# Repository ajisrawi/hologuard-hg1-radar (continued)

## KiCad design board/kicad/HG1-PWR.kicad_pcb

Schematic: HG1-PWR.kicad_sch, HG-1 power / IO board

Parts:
C1: 100u 50V hold-up; CP_Elec_8x10
C2: 100u 50V; CP_Elec_8x10
C100: 47n; C_0402_1005Metric
C101, C104: 100n; C_0402_1005Metric
C102, C105: 1u; C_0402_1005Metric
C103: 47u; C_0805_2012Metric
C106, C108: 4.7u; C_0402_1005Metric
C107: 10u 50V; C_1210_3225Metric
CCH100: 10n 2kV; C_0805_2012Metric
D1: SMCJ36CA; D_SMC
H1, H2, H3, H4: M3; MountingHole_3.2mm_M3_Pad_Via
J1: M12 A-coded 8p power/IO; M12_8P_PCB
J2: M12 X-coded Ethernet; M12_8P_PCB
J3: Micro-Fit to ANT; Molex_Micro-Fit_3.0_43650-0400_1x04_P3.00mm_Horizontal
J4: Micro-Fit to DSP; Molex_Micro-Fit_3.0_43650-0400_1x04_P3.00mm_Horizontal
J5: FFC to DSP; Hirose_FH12-30S-0.5SH_1x30-1MP_P0.50mm_Horizontal
J6: Radome / board heater 10 W; JST_PH_B2B-PH-K_1x02_P2.00mm_Vertical
L1: DM filter 4.7u; L_12x12mm_H6mm
L2: XAL6030 4.7u; L_Coilcraft_XAL6030-XXX
L3: 10u 6A; L_12x12mm_H6mm
L4: 10u; L_0805_2012Metric
L5: XAL6030 2.2u; L_Coilcraft_XAL6030-XXX
Q1: N-MOSFET 80 V pass FET; SOIC-8_3.9x4.9mm_P1.27mm
Q2, Q3, Q4, Q5: N-MOSFET 60 V; SOIC-8_3.9x4.9mm_P1.27mm
Q6: N-MOSFET heater switch; SOIC-8_3.9x4.9mm_P1.27mm
R100, R102, R104, R116: 100k; R_0402_1005Metric
R101: 10k; R_0402_1005Metric
R103: 2.7k; R_0402_1005Metric
R105: 3.3k; R_0402_1005Metric
R106, R109, R113: 1M; R_0402_1005Metric
R107: 73.2k; R_0402_1005Metric
R108, R111: 18.2k; R_0402_1005Metric
R110: 191k; R_0402_1005Metric
R112: 4m 1%; R_0402_1005Metric
R114: 35.7k; R_0402_1005Metric
R115: 402k; R_0402_1005Metric
RCH100: 1M; R_0402_1005Metric
RHT100: 100k; R_0402_1005Metric
RS1: 5m 1%; R_0402_1005Metric
RV1: 150k; R_0402_1005Metric
RV2, RV4, RV5, RV6: 10k; R_0402_1005Metric
RV3: 100k; R_0402_1005Metric
T1: HX1188NL; GBE_MAG_16P
U1: LT4363; DFN-10-1EP_3x3mm_P0.5mm_EP1.65x2.38mm
U2: LT8640S 12 V; QFN-24-1EP_4x4mm_P0.5mm_EP2.6x2.6mm
U3: LT8390 28 V buck-boost; QFN-28-1EP_4x5mm_P0.5mm_EP2.65x3.65mm
U4: LT3462 -5 V; TSOT-23-6
U5: LT8640S 5 V; QFN-24-1EP_4x4mm_P0.5mm_EP2.6x2.6mm
U6: THVD1450; SOIC-8_3.9x4.9mm_P1.27mm

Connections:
+3V3_IO: J5.27, U6.8 (VCC)
+5V_RF: C2.1, J3.2, L4.1, L5.2, R109.1, RV5.1, U4.5 (VIN)
+12V_DSP: C103.1, J4.1, J4.2, L2.2, R106.1
+28V_PA: C107.1, J3.1, R112.2, R113.1, RV3.1, U3.6 (ISN)
-5V_BIAS: C108.1, J5.25, J5.26, R115.1, U4.6 (VOUT)
BG1: Q3.4 (G), U3.21 (BG1)
BG2: Q5.4 (G), U3.23 (BG2)
BST_5: C104.1, U5.13 (BST)
BST_12: C101.1, U2.13 (BST)
CHASSIS: CCH100.1, J1.S1 (SHELL), J1.S2 (SHELL), J1.S3 (SHELL), J1.S4 (SHELL), J2.S1 (SHELL), J2.S2 (SHELL), J2.S3 (SHELL), J2.S4 (SHELL), RCH100.1
DISC_IN: J1.8, J5.17
EN_28V: J5.18, U3.3 (EN/UVLO)
EN_HEATER: J5.21, Q6.4 (G), RHT100.1
EN_NEG5: J5.19, U4.4 (SHDN)
EN_RF_5V: J5.20, U5.3 (EN/UV)
FB_5: R109.2, R110.1, U5.4 (FB)
FB_12: R106.2, R107.1, U2.4 (FB)
FB_28: R113.2, R114.1, U3.4 (FB)
FB_NEG: R115.2, R116.1, U4.3 (FB)
FB_SURGE: R104.2, R105.1, U1.8 (FB)
GND: C1.2, C2.2, C100.2, C102.2, C103.2, C105.2, C106.2, C107.2, C108.2, CCH100.2, D1.2 (A2), H1.1, H2.1, H3.1, H4.1, J1.3, J1.4, J3.3, J3.4, J4.3, J4.4, J5.3, J5.6, J5.9, J5.12, J5.28, J5.29, J5.30, Q3.1 (S), Q3.2 (S), Q3.3 (S), Q5.1 (S), Q5.2 (S), Q5.3 (S), Q6.1 (S), Q6.2 (S), Q6.3 (S), R101.2, R103.2, R105.2, R107.2, R108.2, R110.2, R111.2, R114.2, R116.2, RCH100.2, RHT100.2, RV2.2, RV4.2, RV6.2, U1.5 (GND), U1.11 (GND), U2.17 (GND), U2.25 (GND), U3.13 (GND), U3.29 (GND), U4.2 (GND), U5.17 (GND), U5.25 (GND), U6.2 (~RE), U6.5 (GND)
HEATER_N: J6.2, Q6.5 (D), Q6.6 (D), Q6.7 (D), Q6.8 (D)
INTVCC_5: C105.1, U5.14 (INTVCC)
INTVCC_12: C102.1, U2.14 (INTVCC)
INTVCC_28: C106.1, U3.27 (INTVCC)
ISP_28: Q4.5 (D), Q4.6 (D), Q4.7 (D), Q4.8 (D), R112.1, U3.5 (ISP)
MDI_1: J2.1, T1.9 (CA+)
MDI_2: J2.2, T1.10 (CA-)
MDI_3: J2.3, T1.11 (CB+)
MDI_4: J2.4, T1.12 (CB-)
MDI_5: J2.5, T1.13 (CC+)
MDI_6: J2.6, T1.14 (CC-)
MDI_7: J2.7, T1.15 (CD+)
MDI_8: J2.8, T1.16 (CD-)
OV_DIV: R102.2, R103.1, U1.4 (OV)
PHY_MD1: J5.1, T1.1 (PA+)
PHY_MD2: J5.2, T1.2 (PA-)
PHY_MD3: J5.4, T1.3 (PB+)
PHY_MD4: J5.5, T1.4 (PB-)
PHY_MD5: J5.7, T1.5 (PC+)
PHY_MD6: J5.8, T1.6 (PC-)
PHY_MD7: J5.10, T1.7 (PD+)
PHY_MD8: J5.11, T1.8 (PD-)
PPS_EXT: J1.7, J5.16
RS485_A: J1.5, U6.6 (A)
RS485_B: J1.6, U6.7 (B)
RS485_DE: J5.15, U6.3 (DE)
RS485_RX: J5.14, U6.1 (R)
RS485_TX: J5.13, U6.4 (D)
RT_5: R111.1, U5.5 (RT)
RT_12: R108.1, U2.5 (RT)
SURGE_GATE: Q1.4 (G), U1.6 (GATE)
SW1_28: L3.1, Q2.1 (S), Q2.2 (S), Q2.3 (S), Q3.5 (D), Q3.6 (D), Q3.7 (D), Q3.8 (D), U3.24 (SW1)
SW2_28: L3.2, Q4.1 (S), Q4.2 (S), Q4.3 (S), Q5.5 (D), Q5.6 (D), Q5.7 (D), Q5.8 (D), U3.25 (SW2)
SW_5: C104.2, L5.1, U5.10 (SW), U5.11 (SW)
SW_12: C101.2, L2.1, U2.10 (SW), U2.11 (SW)
SW_NEG: L4.2, U4.1 (SW)
TG1: Q2.4 (G), U3.20 (TG1)
TG2: Q4.4 (G), U3.22 (TG2)
TMR: C100.1, U1.9 (TMR)
UV_DIV: R100.2, R101.1, U1.3 (UV)
V5_SENSE: J5.24, RV5.2, RV6.1
V28_SENSE: J5.23, RV3.2, RV4.1
VIN_FILT: C1.1, J6.1, L1.2, Q2.5 (D), Q2.6 (D), Q2.7 (D), Q2.8 (D), U2.1 (VIN), U2.2 (VIN), U2.3 (EN/UV), U3.1 (VIN), U3.2 (VIN), U5.1 (VIN), U5.2 (VIN)
VIN_PROT: L1.1, R104.1, RS1.2, RV1.1, U1.7 (OUT)
VIN_RAW: D1.1 (A1), J1.1, J1.2, Q1.5 (D), Q1.6 (D), Q1.7 (D), Q1.8 (D), R100.1, R102.1, U1.1 (VCC)
VIN_SENSE: J5.22, RV1.2, RV2.1
VIN_SNS: Q1.1 (S), Q1.2 (S), Q1.3 (S), RS1.1, U1.2 (SNS)

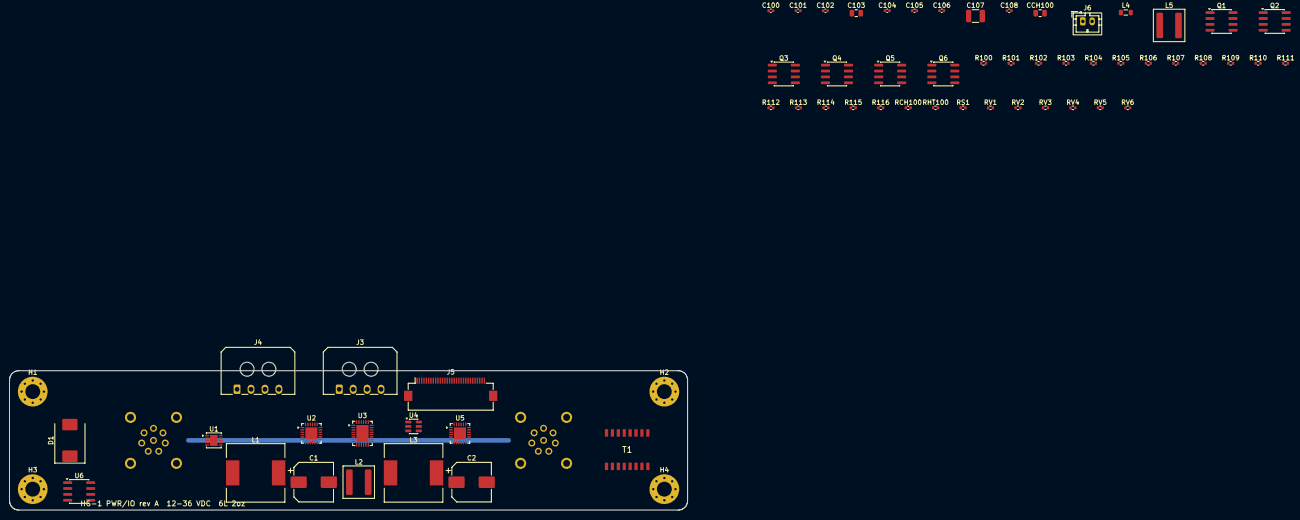
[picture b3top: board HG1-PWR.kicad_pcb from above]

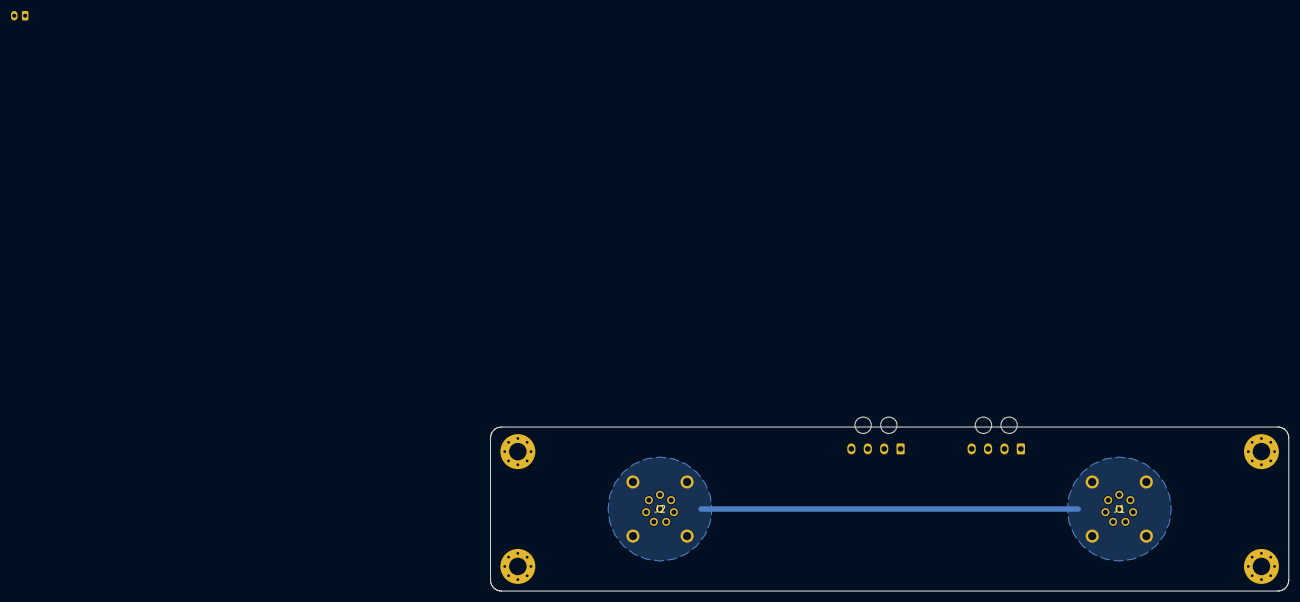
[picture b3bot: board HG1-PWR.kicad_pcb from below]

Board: 6 copper layers, 146.0 x 30.0 mm, 67 parts (2 on the bottom side), 68 nets.

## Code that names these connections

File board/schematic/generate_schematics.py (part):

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    ps.append(Part("Y2", "HG1:OCXO_4P", "33.333 MHz XO (PS_REFCLK)", {"EN": "+1V8", "OUT": "PS_REFCLK",
                   "VCC": "+1V8", "GND": "GND"}, "Oscillator:Oscillator_SMD_EuroQuartz_XO53-4Pin_5.0x3.2mm",
                   group="io"))
    stm = {"PA0": "VIN_SENSE", "PA1": "V28_SENSE", "PA2": "V5_SENSE", "PA3": "V3V3_SENSE", "PC0": "VNEG_SENSE",
           "PB1": "VNEG_SENSE", "PC1": "ID_PA1", "PC2": "ID_PA2", "PC3": "ID_PA3", "PB14": "ID_PA4",
           "PF0": "ID_PA5", "PB12": "ID_PA6", "PB11": "NTC_HOUSING", "PB0": "NTC_RFIC", "PB4": "EN_NEG5",
           "PB5": "EN_28V", "PA8": "EN_DRAIN_SW", "PB7": "EN_RF_5V", "PB6": "TX_MUTE_N", "PC6": "EN_VERSAL",
           "PC7": "EN_HEATER", "PC10": "PLL_LD_TX", "PC11": "PLL_LD_LO", "PC12": "NEG_PGOOD", "PA4": "CS_BF0",
           "PA15": "CS_BF1", "PA5": "MCU_SPI_SCK", "PA6": "MCU_SPI_MISO", "PA7": "MCU_SPI_MOSI",
           "PC8": "I2C3_SCL", "PC9": "I2C3_SDA", "PA9": "UART_M2V", "PA10": "UART_V2M", "PA13": "SWDIO",
           "PA14": "SWCLK", "PG10": "NRST", "VBAT": "+3V3", "VDD": "+3V3", "VDDA": "+3V3", "VREF+": "+3V3",
           "VSS": "GND", "VSSA": "GND"}
    ps.append(Part("U7", "MCU_ST_STM32G4:STM32G474RETx", "STM32G474RET6", stm, "Package_QFP:LQFP-64_10x10mm_P0.5mm",
                   group="mcu"))
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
